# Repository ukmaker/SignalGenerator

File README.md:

# SignalGenerator
Signal generator based on AD9850, AD603 and Arduino Nano

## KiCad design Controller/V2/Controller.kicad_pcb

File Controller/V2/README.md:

Changes from V1:

Correct connection of SDA and SCL to Arduino Nano

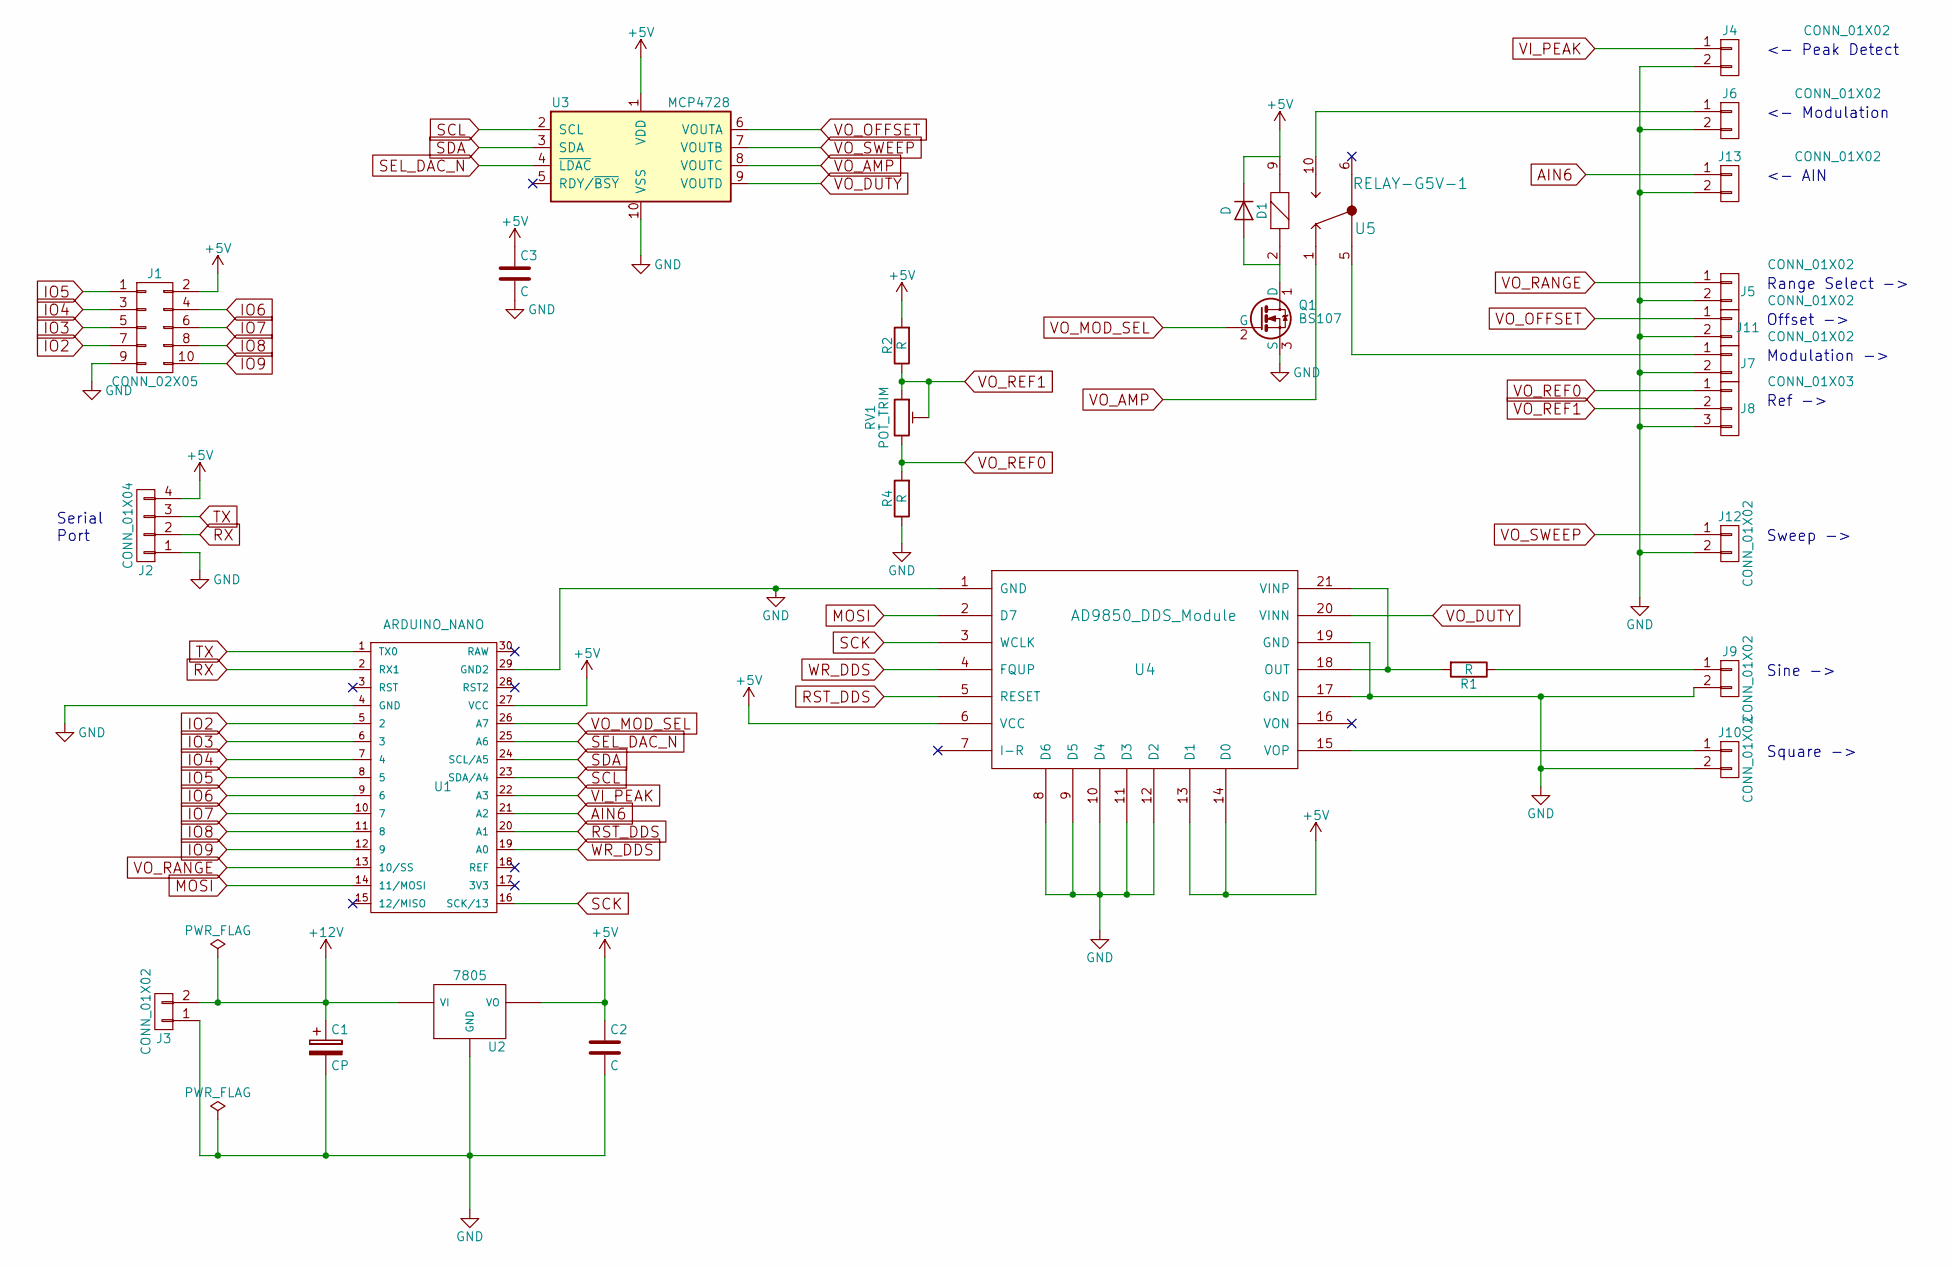
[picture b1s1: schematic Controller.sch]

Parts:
C1: CP; CP_Radial_D5.0mm_P2.50mm
C2, C3: C; C_Disc_D5.0mm_W2.5mm_P5.00mm
D1: D; D_DO-41_SOD81_P7.62mm_Horizontal
J1: CONN_02X05; Pin_Header_Straight_2x05_Pitch2.54mm
J2: CONN_01X04; Pin_Header_Straight_1x04_Pitch2.54mm
J3, J4, J5, J6, J7, J9, J10, J11, J12, J13: CONN_01X02; Pin_Header_Straight_1x02_Pitch2.54mm
J8: CONN_01X03; Pin_Header_Straight_1x03_Pitch2.54mm
Q1: BS107; TO-92_Inline_Wide
R1, R2, R4: R; R_Axial_DIN0207_L6.3mm_D2.5mm_P7.62mm_Horizontal
RV1: POT_TRIM; Potentiometer_Trimmer_Bourns_3005
U1: ARDUINO_NANO; Arduino_nano
U2: 7805; 7805-TO-220_Vertical
U3: MCP4728; DIP-10_W7.62mm
U4: AD9850_DDS_Module
U5: RELAY-G5V-1; SparkFun-RELAY-G5V

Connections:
+5V: C2.1, C3.1, D1.1 (K), J1.2, J2.4, R2.2, U1.27 (VCC), U2.VO, U3.1 (VDD), U4.6 (VCC), U4.13 (D1), U4.14 (D0), U5.9
+12V: C1.1, J3.2, U2.VI
AIN6: J13.1, U1.21 (A2)
GND: C1.2, C2.2, C3.2, J1.9, J2.1, J3.1, J4.2, J5.2, J6.2, J7.2, J8.3, J9.2, J10.2, J11.2, J12.2, J13.2, Q1.3 (S), R4.1, U1.4 (GND), U1.29 (GND2), U2.GND, U3.10 (VSS), U4.1 (GND), U4.8 (D6), U4.9 (D5), U4.10 (D4), U4.11 (D3), U4.12 (D2), U4.17 (GND), U4.19 (GND)
IO2: J1.7, U1.5 (2)
IO3: J1.5, U1.6 (3)
IO4: J1.3, U1.7 (4)
IO5: J1.1, U1.8 (5)
IO6: J1.4, U1.9 (6)
IO7: J1.6, U1.10 (7)
IO8: J1.8, U1.11 (8)
IO9: J1.10, U1.12 (9)
MOSI: U1.14 (11/MOSI), U4.2 (D7)
unnamed: D1.2 (A), Q1.1 (D), U5.2
unnamed: J6.1, U5.10
unnamed: J7.1, U5.5
unnamed: J9.1, R1.1
unnamed: J10.1, U4.15 (VOP)
unnamed: R1.2, U4.18 (OUT), U4.21 (VINP)
RST_DDS: U1.20 (A1), U4.5 (RESET)
RX: J2.2, U1.2 (RX1)
SCK: U1.16 (SCK/13), U4.3 (WCLK)
SCL: U1.23 (SDA/A4), U3.2 (SCL)
SDA: U1.24 (SCL/A5), U3.3 (SDA)
SEL_DAC_N: U1.25 (A6), U3.4 (~LDAC)
TX: J2.3, U1.1 (TX0)
VI_PEAK: J4.1, U1.22 (A3)
VO_AMP: U3.8 (VOUTC), U5.1
VO_DUTY: U3.9 (VOUTD), U4.20 (VINN)
VO_MOD_SEL: Q1.2 (G), U1.26 (A7)
VO_OFFSET: J11.1, U3.6 (VOUTA)
VO_RANGE: J5.1, U1.13 (10/SS)
VO_REF0: J8.1, R4.2, RV1.3
VO_REF1: J8.2, R2.1, RV1.1, RV1.2
VO_SWEEP: J12.1, U3.7 (VOUTB)
WR_DDS: U1.19 (A0), U4.4 (FQUP)

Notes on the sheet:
Serial Port
<- Peak Detect
Range Select ->
Offset ->
<- Modulation
Modulation ->
Ref ->
Sweep ->
Sine ->
Square ->
<- AIN

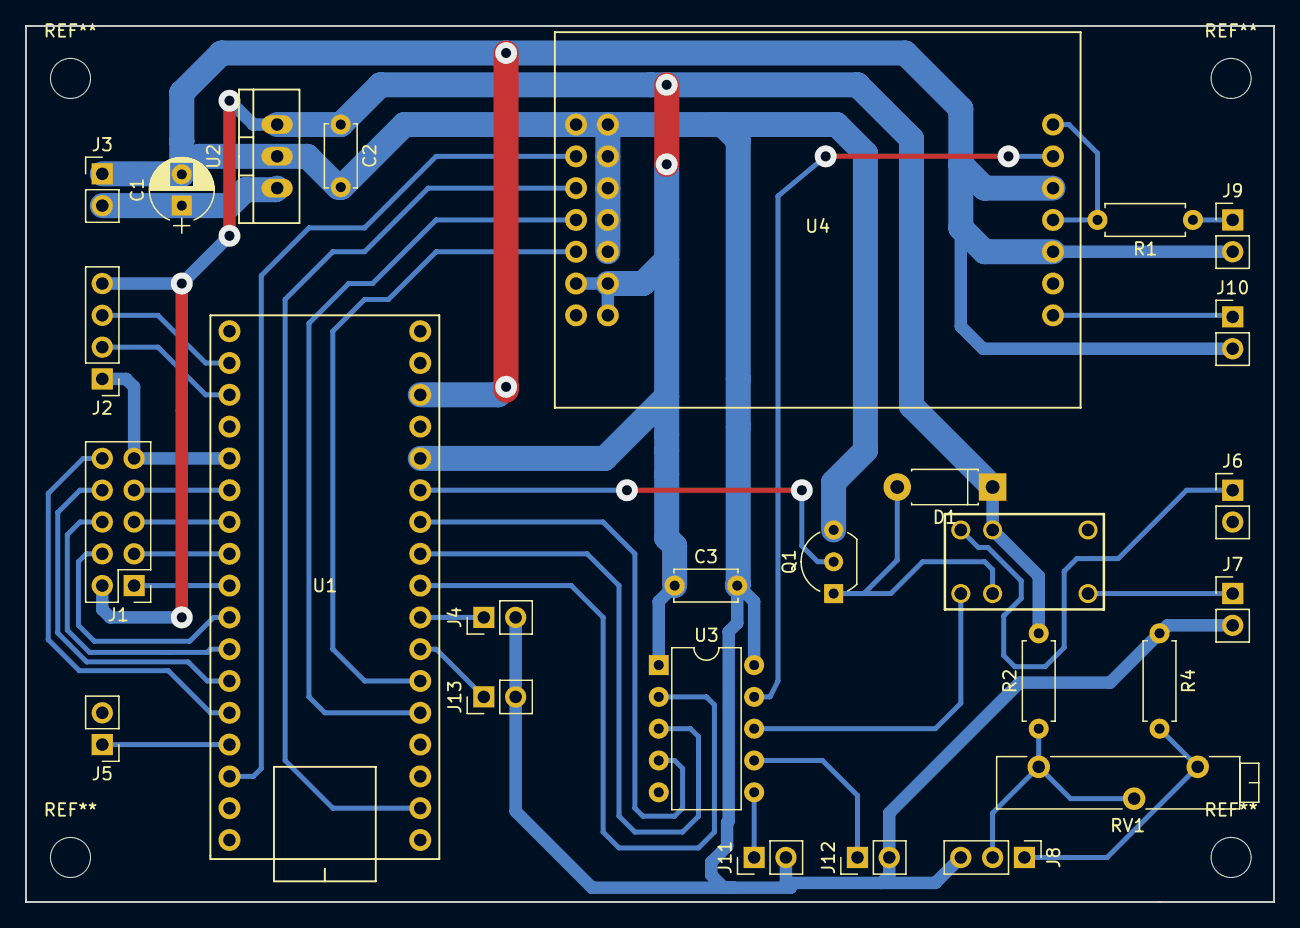
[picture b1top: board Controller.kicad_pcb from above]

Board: 2 copper layers, 99.7 x 70.0 mm, 27 parts (0 on the bottom side), 36 nets.

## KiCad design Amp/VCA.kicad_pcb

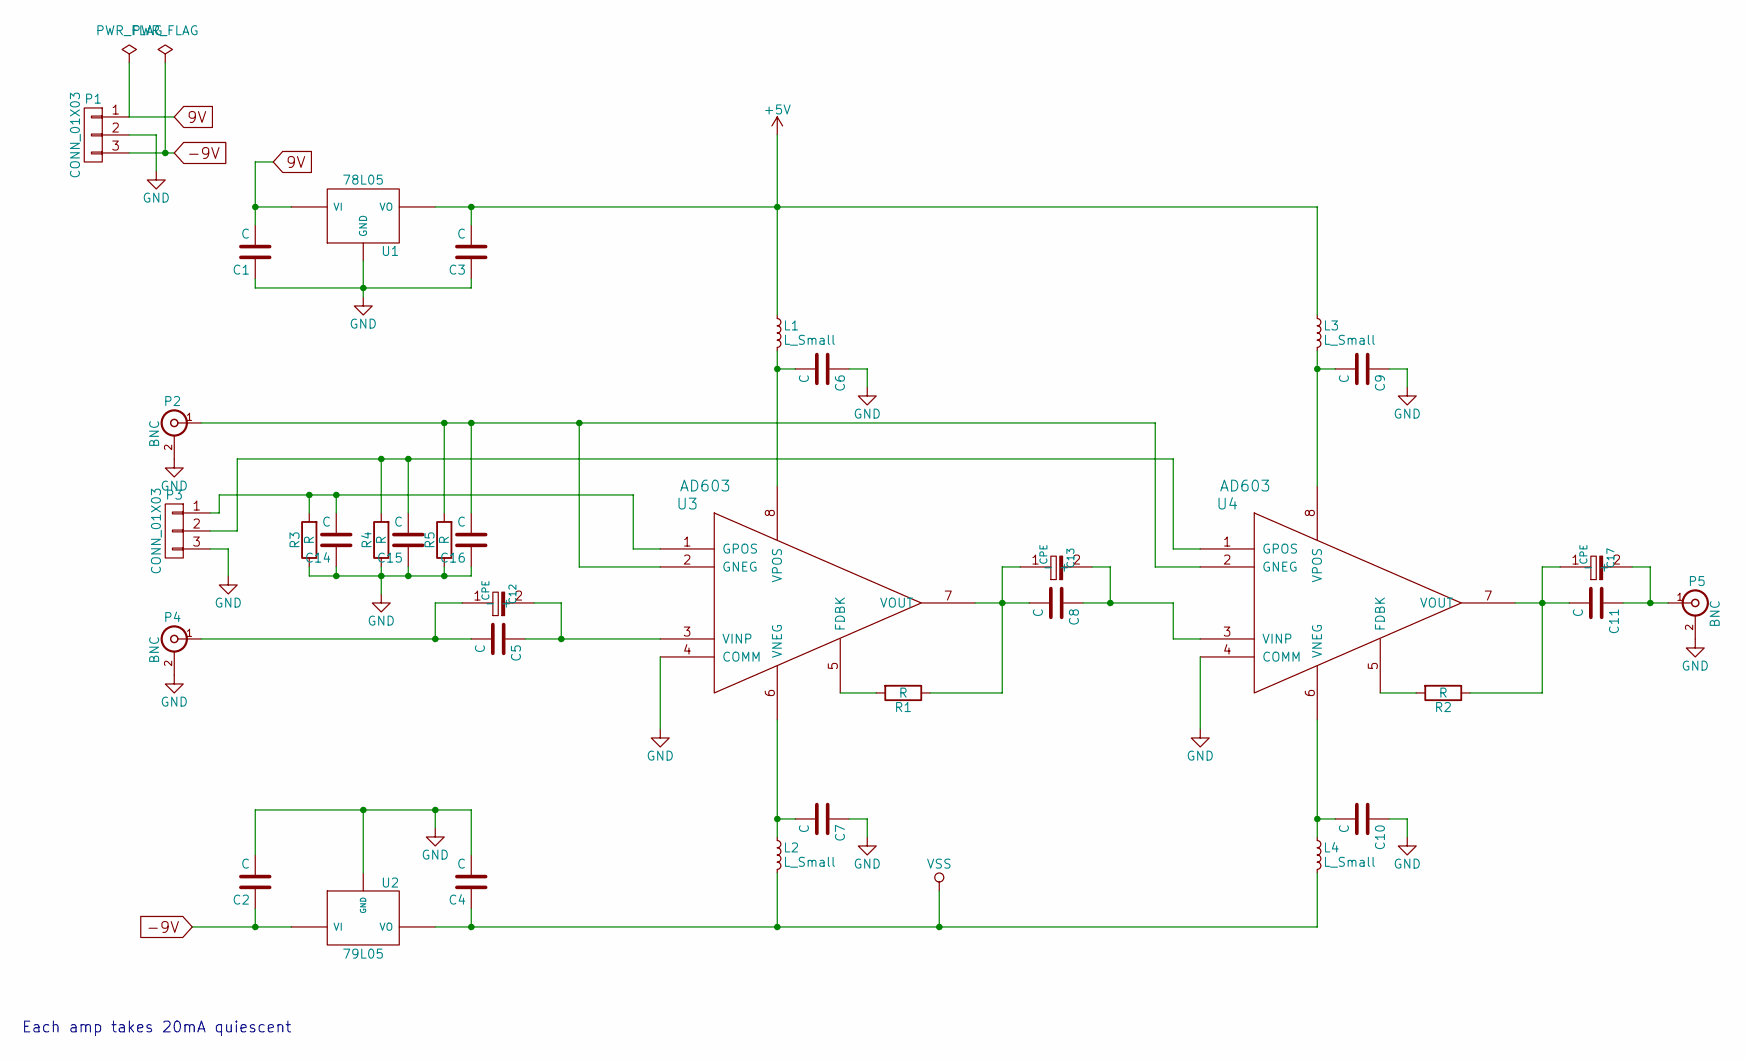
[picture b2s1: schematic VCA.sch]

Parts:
C1, C2, C3, C4, C5, C6, C7, C8, C9, C10, C11, C14, C15, C16: C; C_Disc_D4.3mm_W1.9mm_P5.00mm
C12, C13, C17: CPE; CP_Radial_D5.0mm_P2.50mm
L1, L2, L3, L4: L_Small; Choke_Horizontal_RM10mm
P1, P3: CONN_01X03; Pin_Header_Straight_1x03_Pitch2.54mm
P2, P4, P5: BNC; Pin_Header_Straight_1x02_Pitch2.54mm
R1, R2, R3, R4, R5: R; R_Axial_DIN0207_L6.3mm_D2.5mm_P10.16mm_Horizontal
U1: 78L05; LM78LXX-H
U2: 79L05; LM79LXX-H
U3, U4: AD603; SOIC-8-N-Hand-Soldering

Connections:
9V: C1.2, P1.1, U1.VI
+5V: C3.2, L1.1, L3.1, U1.VO
-9V: C2.1, P1.3, U2.VI
GND: C1.1, C2.2, C3.1, C4.2, C6.1, C7.1, C9.1, C10.1, C14.1, C15.1, C16.1, P1.2, P2.2 (Ext), P3.3, P4.2 (Ext), P5.2 (Ext), R3.1, R4.1, R5.1, U1.GND, U2.GND, U3.4 (COMM), U4.4 (COMM)
unnamed: C6.2, L1.2, U3.8 (VPOS)
unnamed: C7.2, L2.1, U3.6 (VNEG)
unnamed: C9.2, L3.2, U4.8 (VPOS)
unnamed: C10.2, L4.1, U4.6 (VNEG)
unnamed: C11.1, C17.2 (-), P5.1 (In)
unnamed: C11.2, C17.1 (+), R2.1, U4.7 (VOUT)
unnamed: C5.2, C12.1 (+), P4.1 (In)
unnamed: C5.1, C12.2 (-), U3.3 (VINP)
unnamed: C8.2, C13.1 (+), R1.1, U3.7 (VOUT)
unnamed: C8.1, C13.2 (-), U4.3 (VINP)
unnamed: C14.2, P3.1, R3.2, U3.1 (GPOS)
unnamed: C15.2, P3.2, R4.2, U4.1 (GPOS)
unnamed: C16.2, P2.1 (In), R5.2, U3.2 (GNEG), U4.2 (GNEG)
unnamed: R1.2, U3.5 (FDBK)
unnamed: R2.2, U4.5 (FDBK)
VSS: C4.1, L2.2, L4.2, U2.VO

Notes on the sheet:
Each amp takes 20mA quiescent

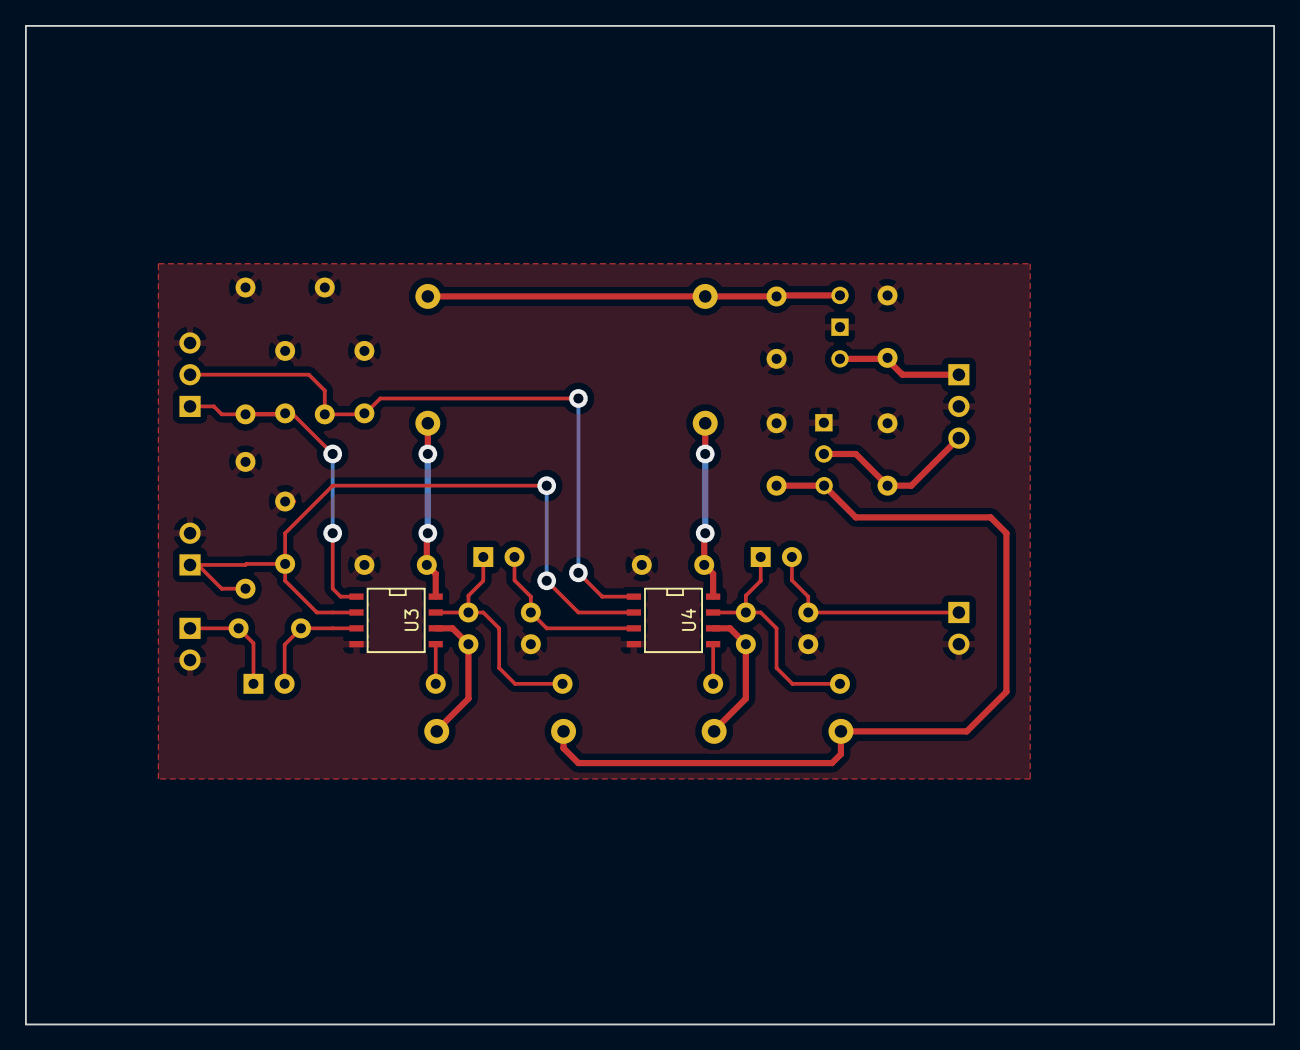
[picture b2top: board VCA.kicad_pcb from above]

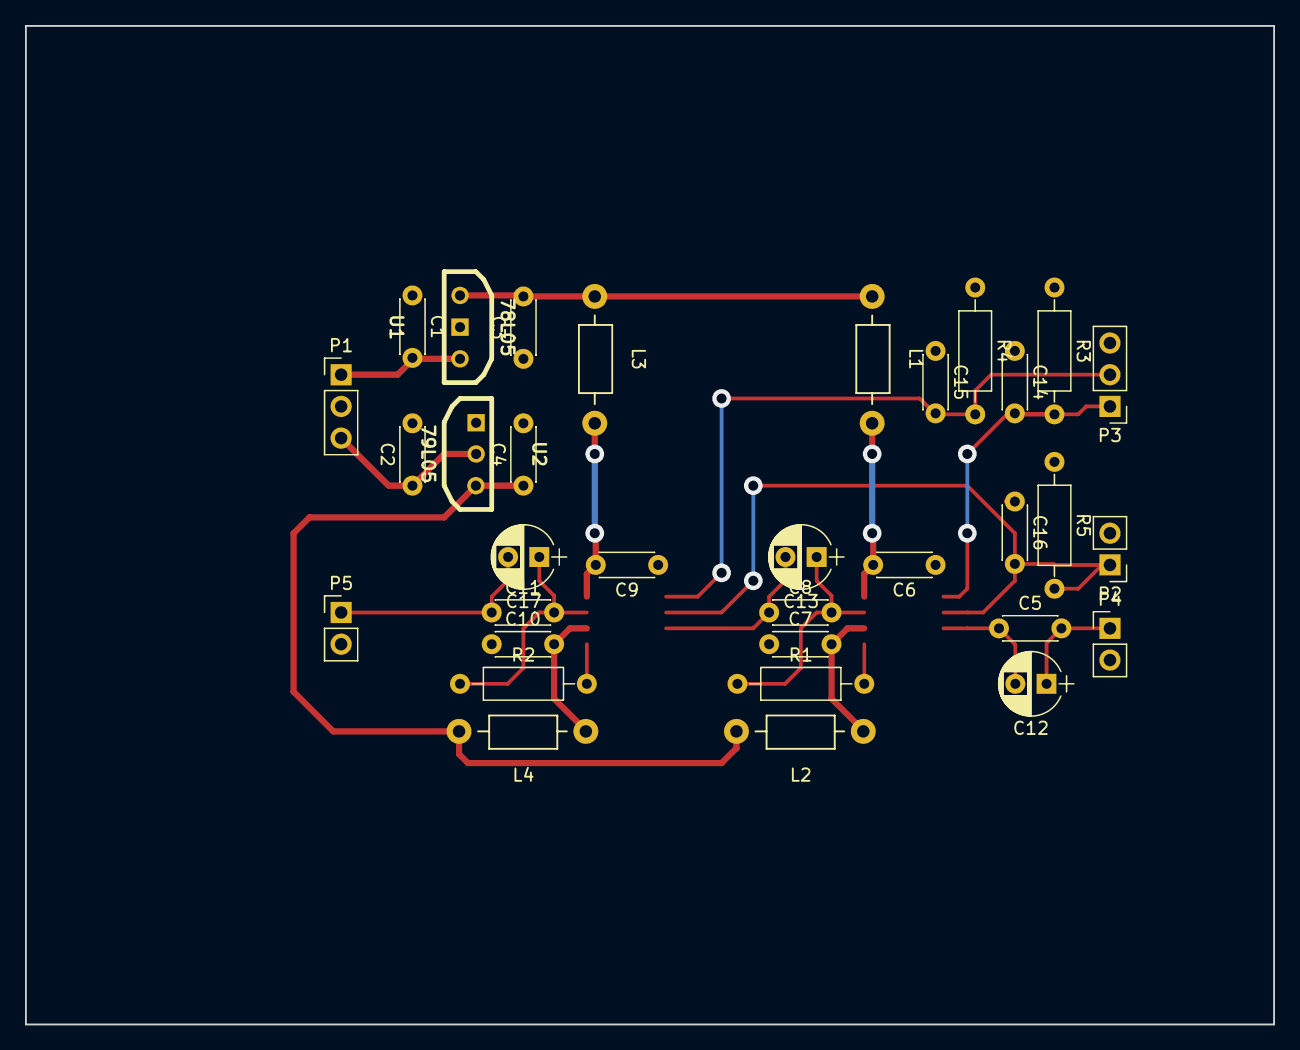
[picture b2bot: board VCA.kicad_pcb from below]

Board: 2 copper layers, 100.0 x 80.0 mm, 35 parts (33 on the bottom side), 20 nets.

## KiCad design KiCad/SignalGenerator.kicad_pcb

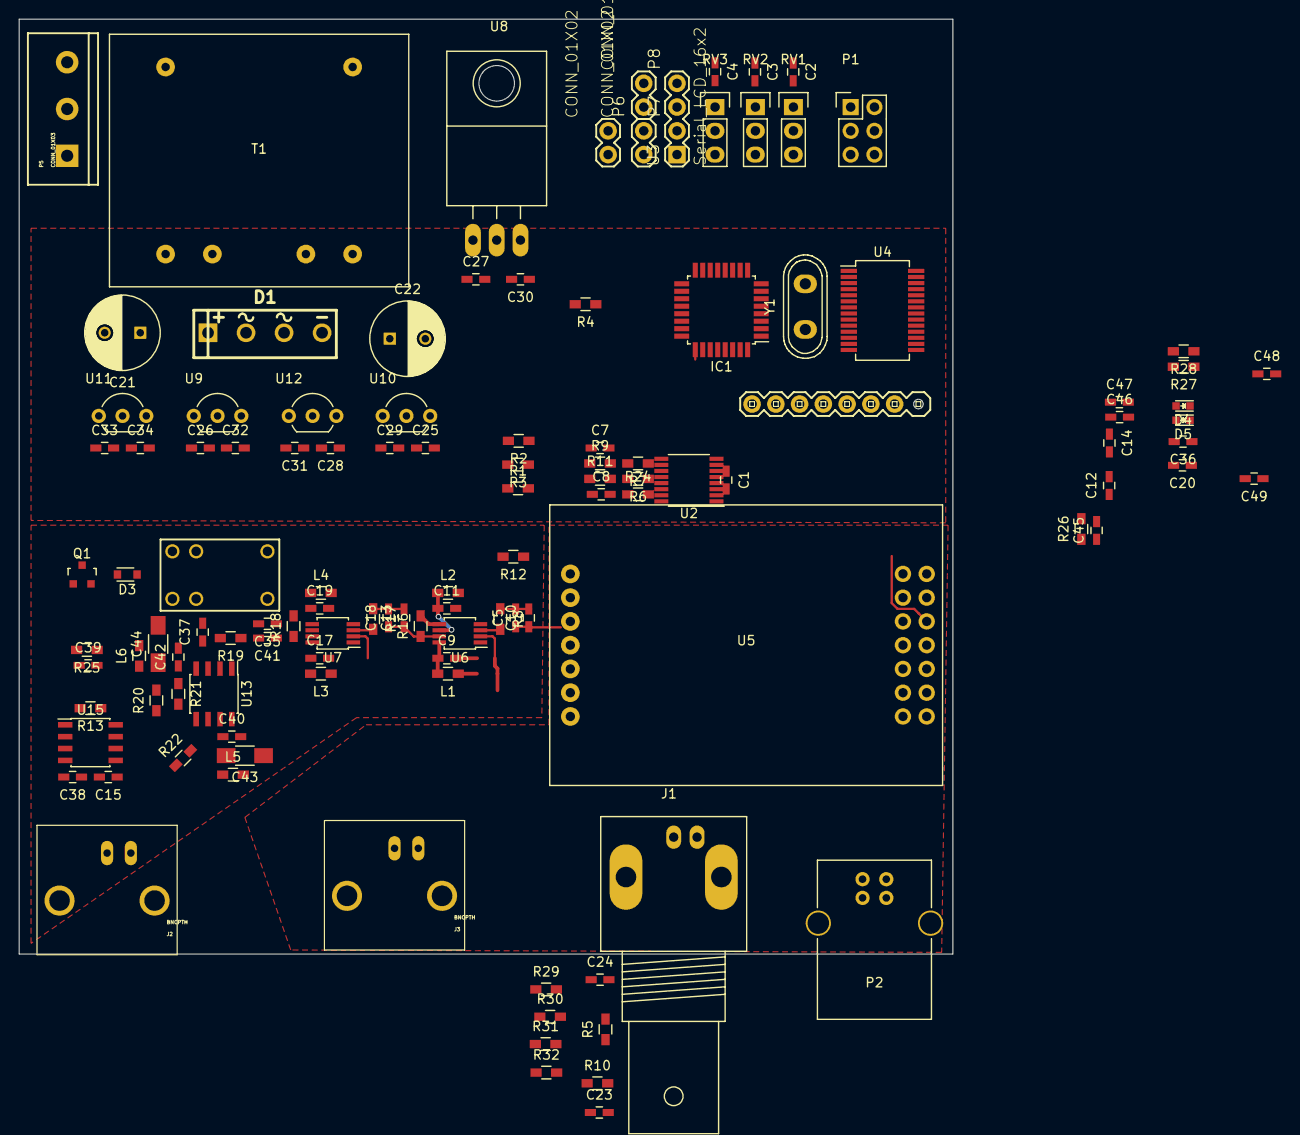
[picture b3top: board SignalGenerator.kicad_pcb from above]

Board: 2 copper layers, 99.8 x 99.9 mm, 117 parts (0 on the bottom side), 87 nets.

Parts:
C1, C2, C3, C4, C12, C14, C20, C36, C48, C49: Csmall; C_0603_HandSoldering
C5, C7, C8, C9, C11, C13, C15, C17, C19, C23, C24, C25, C26, C27, C28, C29, C30, C31, C32, C33, C34, C35, C37, C38, C39, C40, C42, C45, C46, C47: C; C_0603_HandSoldering
C10, C18, C41: 1U MLCC; C_0603_HandSoldering
C21, C22: CP; C_Radial_D8_L13_P3.8
C43, C44: 10U MLCC; C_1206_HandSoldering
D1: KBP206G; BridgeRectifier_2KBP
D3: D; D_0805
D4, D5: LED; LED_0603
IC1: ATMEGA328-A; TQFP-32_7x7mm_Pitch0.8mm
J1: BNCPTH; BNC_Socket_TYCO-AMP_LargePads
J2, J3: BNCPTH; BNC
L1, L2, L3, L4, L5, L6: L_Small; R_0603_HandSoldering
P1: CONN_02X03; Pin_Header_Straight_2x03
P2: USB_B
P5: CONN_01X03; SCREWTERMINAL-5MM-3
P6, P7, P8: CONN_01X02; 1X02
Q1: Q_NMOS_SDG; SOT-23
R1, R2, R3, R4, R5, R6, R7, R9, R10, R11, R12, R13, R17, R19, R20, R21, R22, R24, R25, R26, R27, R28, R29, R30, R31, R32: R; R_0603_HandSoldering
R8: 1k5; R_0603_HandSoldering
R16, R18: 0R; R_0603_HandSoldering
RV1, RV2, RV3: POT; Pin_Header_Straight_1x03
T1: TRANSFO2; MyrraTransformer_30x15.5
U1: Tri-Colour_Rotary_Encoder; SparkFun-1X08
U2: AD5592R; TSSOP-16_4.4x5mm_Pitch0.65mm
U3: Serial_LCD_16x2; 1X04
U4: FT232RLSSOP; SSOP-28_5.3x10.2mm_Pitch0.65mm
U5: AD9850_DDS_Module
U6, U7: AD603; MSOP-8_3x3mm_Pitch0.65mm
U8: 7805; TO-220_Neutral123_Horizontal_LargePads
U9, U11: 7805; TO-92_Inline_Wide
U10, U12: 7905; TO-92_Inline_Wide
U13, U15: LM741; SOIC-8_3.9x4.9mm_Pitch1.27mm
U16: RELAY-G5V-1; SparkFun-RELAY-G5V
Y1: Crystal_Small; Crystal_HC50-U_Vertical

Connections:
+5VA: C31.1, L1.1, L3.1
+5VD: C1.2, C12.2, C14.2, C20.2, C30.1, C48.2, C49.2, D3.1, IC1.4, IC1.6, IC1.18, P1.2, R26.1, R27.1, R28.1, RV1.1, RV2.1, RV3.1, U1.4, U2.1, U2.3, U3.2, U4.4, U4.20, U5.6, U5.13, U5.14, U16.9
+15V: C15.1, C33.1, L5.2, R5.1, U15.7
-5VA: C32.2, L2.2, L4.2
/AnalogBoard/ADC1: P7.1, U2.13
/AnalogBoard/AMPLITUDE_DAC: R29.1, U2.7
/AnalogBoard/DAC0: P6.1, U2.11
/AnalogBoard/DDS_D7: IC1.12, U5.2
/AnalogBoard/DUTY_DAC: R7.1, U2.10
/AnalogBoard/GNEG0_DAC: R30.1, U2.5
/AnalogBoard/GNEG1_DAC: R6.1, U2.6
/AnalogBoard/MODULATION: IC1.24, Q1.3
/AnalogBoard/OFFSET_DAC: R24.2, U2.4
/AnalogBoard/RESET_DDS: IC1.25, U5.5
/ControlBoard/A1: C2.2, IC1.19, RV1.2
/ControlBoard/A2: C3.2, IC1.22, RV2.2
/ControlBoard/A3: C4.2, IC1.26, RV3.2
/ControlBoard/ADC0: P8.1, U2.12
/ControlBoard/ADSEL: IC1.23, U2.2
/ControlBoard/D2: IC1.32, U1.1
/ControlBoard/D3: IC1.1, U1.3
/ControlBoard/D4: IC1.2, R2.1
/ControlBoard/D5: IC1.9, R3.1
/ControlBoard/D6: IC1.10, R1.1, U1.6
/ControlBoard/D7: IC1.11, R4.1
/ControlBoard/DDS_FQUP: IC1.14, U5.4
/ControlBoard/DDS_WCLK: IC1.13, U5.3
/ControlBoard/DTR: C45.2, IC1.29, P1.5, R26.2, U4.2
/ControlBoard/MISO: IC1.16, P1.1, U2.9
/ControlBoard/MOSI: IC1.15, P1.4, U2.15
/ControlBoard/RXD: IC1.30, U4.1
/ControlBoard/SCK: IC1.17, P1.3, U2.16
/ControlBoard/SCL: IC1.28, U3.4
/ControlBoard/SDA: IC1.27, U3.3
/ControlBoard/TXD: IC1.31, U4.5
/PSU/LIVE: P5.3, T1.1
/PSU/NEUTRAL: P5.2, T1.2
AMPLITUDE: C24.2, R29.2, R32.2, U16.10
DDS_OUT: C5.1, C10.1, U5.18, U5.20
DUTY_CYCLE: C7.2, R7.2, R9.2, U5.21
GND: C1.1, C2.1, C3.1, C4.1, C7.1, C8.1, C9.2, C11.2, C12.1, C14.1, C15.2, C17.2, C19.2, C20.1, C21.2, C22.1, C23.1, C24.1, C25.2, C26.1, C27.2, C28.2, C29.1, C30.2, C31.2, C32.1, C33.2, C34.1, C36.1, C37.2, C38.1, C39.1, C40.2, C42.2, C43.1, C44.2, C45.1, C46.1, C47.1, C48.1, C49.1, IC1.3, IC1.5, IC1.21, J2.GND, J3.GND, P1.6, P2.4, P2.5, P5.1, P6.2, P7.2, P8.2, Q1.1, R1.2, R9.1, R10.2, R11.1, R31.1, R32.1, RV1.3, RV2.3, RV3.3, T1.4, T1.5, U1.2, U2.14, U3.1, U4.7, U4.18, U4.21, U4.25, U4.26, U5.1, U5.8, U5.9, U5.10, U5.11, U5.12, U5.17, U5.19, U6.4, U7.4
GNEG0: C23.2, R30.2, R31.2, U6.2
GNEG1: C8.2, R6.2, R11.2, U7.2
unnamed: C9.1, L1.2, U6.8
unnamed: C5.2, C10.2, R8.1
unnamed: C11.1, L2.1, U6.6
unnamed: C13.1, C18.1, R16.1, U6.7
unnamed: C13.2, C18.2, R17.1
unnamed: C17.1, L3.2, U7.8
unnamed: C19.1, L4.1, U7.6
unnamed: C21.1, C25.1, C27.1, C28.1, D1.3
unnamed: C22.2, C26.2, C29.2, D1.1
unnamed: C35.1, C41.1, R18.1, U7.7
unnamed: C35.2, C41.2, R19.1
unnamed: C36.2, IC1.20
unnamed: C37.1, R20.2, U13.3
unnamed: C38.2, U15.4
unnamed: C39.2, R24.1, U15.3
unnamed: C40.1, C43.2, L5.1, U13.7
unnamed: C42.1, C44.1, L6.1, U13.4
unnamed: C46.2, IC1.7, Y1.1
unnamed: C47.2, IC1.8, Y1.2
unnamed: D1.2, T1.6
unnamed: D1.4, T1.3
unnamed: D3.2, Q1.2, U16.2
unnamed: D4.1, U4.23
unnamed: D4.2, R27.2
unnamed: D5.1, U4.22
unnamed: D5.2, R28.2
unnamed: J2.S, R22.2
unnamed: J3.S, U16.1
unnamed: P2.2, U4.16
unnamed: P2.3, U4.15
unnamed: R2.2, U1.8
unnamed: R3.2, U1.7
unnamed: R4.2, U1.5
unnamed: R8.2, U6.3
unnamed: R5.2, R10.1, R25.2
unnamed: R12.1, U5.15
unnamed: R13.1, R20.1, U15.6
unnamed: R13.2, R25.1, U15.2
unnamed: R16.2, U6.5
unnamed: R17.2, U7.3
unnamed: R18.2, U7.5
unnamed: R19.2, R21.1, U13.2
unnamed: R21.2, R22.1, U13.6
unnamed: U6.1, U7.1, U16.6

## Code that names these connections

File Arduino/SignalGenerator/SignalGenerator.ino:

#include <mcp4728.h>
#include <EEPROM.h>

// Pins to control the DDS module
#define SCK 13      // connect to AD9850 module word load clock pin (CLK)
#define WR_DDS 15      // connect to freq update pin (FQ)
#define MOSI 11       // connect to serial data load pin (MOSI)
#define RST_DDS 14  // connect to reset pin (RST) 

// Pins to control the DAC
#define SDA A5
#define SCL A4
#define SEL_DAC_N 10

// Other control pins
#define VI_PEAK A7
#define AIN6 A6
#define VO_RANGE A3
#define VO_MOD_SEL A2

#define F1MHZ 1000000

// DAC channels
#define VO_AMP 0
#define VO_REF0 1
#define VO_REF1 2
#define VO_DUTY 3

// Application state

int stat = 0;

#define MODE_MANUAL 0
#define MODE_SWEEP 2
#define MODE_SET_FREQUENCY 3
#define MODE_SET_LOW 4
#define MODE_SET_HIGH 5
#define MODE_SET_INCREMENT 6
#define MODE_SET_SWEEP_TYPE 7
#define MODE_SET_GAIN 8


#define SWEEP_TYPE_LINEAR 0
#define SWEEP_TYPE_LOG 1

int_fast32_t sweepLow = 1;
int_fast32_t sweepHigh = 1;
int_fast32_t sweepIncrement = 1;
int_fast32_t sweepStep = 1;
int_fast32_t sweepDecade = 1;
int mode = MODE_MANUAL;
int sweepType = SWEEP_TYPE_LOG;

unsigned long lastMillis = 0;

#define pulseHigh(pin) {digitalWrite(pin, HIGH); digitalWrite(pin, LOW); }

mcp4728 dac = mcp4728(0); // instantiate mcp4728 object, Device ID = 0

int_fast32_t frequency = 7000000; // Starting frequency of VFO
int_fast32_t frequency2 = 1; // variable to hold the updated frequency
int_fast32_t increment = 0; // starting VFO update increment in HZ.

int_fast32_t sf = 0;


#define MAX_FREQUENCY 45000000
#define MIN_FREQUENCY 2

byte ones, tens, hundreds, thousands, tenthousands, hundredthousands, millions = 0; //Placeholders

String incrementUnits;

int_fast32_t timepassed = millis(); // int to hold the arduino miilis since startup
int memstatus = 1;  // value to notify if memory is current or old. 0=old, 1=current.
int ForceFreq = 0;  // Change this to 0 after you upload and run a working sketch to activate the EEPROM memory.  YOU MUST PUT THIS BACK TO 0 AND UPLOAD THE SKETCH AGAIN AFTER STARTING FREQUENCY IS SET!

boolean out = true;


char buff[200];

int calTableIdx = 0;
int lastCalTableIdx = 0;


/**
   Addresses in EEPROM where various values are stored
*/
#define FREQUENCY_ADDR 0
#define INCREMENT_ADDR (FREQUENCY_ADDR + sizeof(frequency))
#define CALIBRATED_ADDR (INCREMENT_ADDR + sizeof(increment))
#define VS_CAL_ADDR (CALIBRATED_ADDR + sizeof(calibrated))
#define VC_CAL_ADDR (VS_CAL_ADDR + sizeof(vsCal))

void setup() {

  Serial.begin(38400);

  setupDDS();
  setupDAC();
  setupControlPins();

  if (!ForceFreq) {
    EEPROM.get(FREQUENCY_ADDR, frequency);
  }

  EEPROM.get(INCREMENT_ADDR, increment);


  setIncrementUnits();
  setFrequency(frequency);
  updateFrequency();

}

void setupControlPins() {
  pinMode(VO_RANGE, OUTPUT);
  digitalWrite(VO_RANGE, 0);

  pinMode(VO_MOD_SEL, OUTPUT);
  digitalWrite(VO_MOD_SEL, 0);
}


void setupDDS() {
  pinMode(WR_DDS, OUTPUT);
  pinMode(SCK, OUTPUT);
  pinMode(MOSI, OUTPUT);
  pinMode(RST_DDS, OUTPUT);
  pulseHigh(RST_DDS);
  pulseHigh(SCK);
  pulseHigh(WR_DDS);  // Enable serial mode. Shouldn't be necessary since the pins are tied.

}

void setupDAC() {
  dac.begin();  // initialize i2c interface
  dac.vdd(5000); // set VDD(mV) of MCP4728 for correct conversion between LSB and Vout
  dac.setVref(1, 1, 1, 1); // set to use internal voltage reference (2.048V)
  dac.setGain(1, 1, 1, 1); // set to use internal voltage reference (4.096V)
  dac.voutWrite(2500, 2500, 2500, 2500);
  // Set up a 1V offset between the VGAs for sequential gain
  dac.voutWrite(VO_REF0, 2000);
  dac.voutWrite(VO_REF1, 3000);
}


// frequency calc from datasheet page 8 = <sys clock> * <frequency tuning word>/2^32
void setFrequency(double frequency) {

  // note 125 MHz clock on 9850.  You can make 'slight' tuning variations here by adjusting the clock frequency.
  int32_t freq = frequency * 4294967295 / 125000000;

  for (int b = 0; b < 4; b++, freq >>= 8) {
    tfr_byte(freq & 0xFF);
  }

  tfr_byte(0x000);   // Final control byte, all 0 for 9850 chip
  pulseHigh(WR_DDS);  // Done!  Should see output
}

// transfers a byte, a bit at a time, LSB first to the 9850 via serial MOSI line
void tfr_byte(byte data) {

  for (int i = 0; i < 8; i++, data >>= 1) {
    digitalWrite(MOSI, data & 0x01);
    pulseHigh(SCK);   //after each bit sent, CLK is pulsed high
  }
}

void nextIncrement() {

  increment = increment * 10L;

  if (increment > 10000000L) {
    increment = 1L;
  }
}

void setIncrementUnits() {

  if (increment == 10L) {
    incrementUnits = " 10 Hz";
  } else if (increment == 100L) {
    incrementUnits = "100 Hz";
  } else if (increment == 1000L) {
    incrementUnits = "  1 KHz";
  } else if (increment == 10000L) {
    incrementUnits = " 10 KHz";
  } else if (increment == 100000L) {
    incrementUnits = "100 KHz";
  } else if (increment == 1000000L) {
    incrementUnits = "  1 MHz";
  } else {
    incrementUnits = "  1 Hz";
  }
}

void updateFrequency() {

  millions = int(frequency / 1000000);
  hundredthousands = ((frequency / 100000) % 10);
  tenthousands = ((frequency / 10000) % 10);
  thousands = ((frequency / 1000) % 10);
  hundreds = ((frequency / 100) % 10);
  tens = ((frequency / 10) % 10);
  ones = ((frequency / 1) % 10);

  timepassed = millis();
  memstatus = 0; // Trigger memory write
}

void loop() {

  handleSerial();
  handleSweep();

  if (frequency != frequency2) {
    setFrequency(frequency);
    frequency2 = frequency;
  }
}


void handleSerial() {
  while(Serial.available()) {
    char c = Serial.read();
    switch (mode) {

      case MODE_MANUAL:

        if (c == 'F') {
          mode = MODE_SET_FREQUENCY;
          sf = 0;
          break;
        }

        if (c == 'L') {
          mode = MODE_SET_LOW;
          sf = 0;
          break;
        }

        if (c == 'H') {
          mode = MODE_SET_HIGH;
          sf = 0;
          break;
        }

        if (c == 'I') {
          mode = MODE_SET_INCREMENT;
          sf = 0;
          break;
        }

        if (c == 'T') {
          mode = MODE_SET_SWEEP_TYPE;
          break;
        }

        if (c == 'G') {
          mode = MODE_SET_GAIN;
          sf = 0;
          break;
        }

        break;

      case MODE_SET_FREQUENCY:
        if (lastDigit(c)) frequency = sf;
        break;

      case MODE_SET_LOW:
        if (lastDigit(c)) sweepLow = sf;
        break;

      case MODE_SET_HIGH:
        if (lastDigit(c)) sweepHigh = sf;
        break;

      case MODE_SET_INCREMENT:
        if (lastDigit(c)) {
          sweepIncrement = sf;
          sweepStep = sweepIncrement;
        }
        break;

      case MODE_SET_SWEEP_TYPE:
        if (c == 'L') {
          sweepType = SWEEP_TYPE_LINEAR;
        } else {
          sweepType = SWEEP_TYPE_LOG;
          sweepDecade = 1;
        }
        mode = MODE_SWEEP;

        frequency = sweepLow;
        Serial.println("Sweep");
        Serial.println(sweepLow);
        Serial.println(sweepHigh);
        Serial.println(sweepIncrement);
        Serial.println(sweepType);
        break;

      case MODE_SWEEP:
        if (c != '\r') mode = MODE_MANUAL;
        break;

      case MODE_SET_GAIN:
       if(lastDigit(c)) dac.voutWrite(VO_AMP, sf);
       break;

      default:
        mode = MODE_MANUAL;
        break;

    }

  }
}

void handleSweep() {
  if (mode == MODE_SWEEP) {
    delay(500);
    if (sweepType == SWEEP_TYPE_LINEAR) {
      frequency += sweepIncrement;
      if (frequency > sweepHigh) {
        frequency = sweepLow;
      }
    } else {

      frequency += sweepStep;
      if (sweepDecade == 9) {
        sweepDecade = 1;
        sweepStep = sweepStep * 10;
      } else {
        sweepDecade++;
      }

      if(frequency > sweepHigh) {
        frequency = sweepLow;
        sweepStep = sweepIncrement;
        sweepDecade = 1;
      }

    }
    float x = 4096 * (float)(frequency - sweepLow) / (float)(sweepHigh - sweepLow);
    Serial.println(x);
  }
}

bool lastDigit(char c) {
  if (c == '\r') {
    mode = MODE_MANUAL;
    return true; // done with digits
  }
  if (c >= '0' && c <= '9') {
    sf = (sf * 10) + c - '0';
  } else {
    mode = MODE_MANUAL;
  }

  return false;
}

void printStatus() {
  stat++;
  if (stat < 400) return;
  stat = 0;
}

void storeMEM() {
  EEPROM.put(0, frequency);
  EEPROM.put(INCREMENT_ADDR, increment);
  memstatus = 1;  // Let program know memory has been written
};

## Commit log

2017-05-07 Initial import
2017-08-12 Started to refactor code to use bettwe widget event handling Created UILib for use in future projects
